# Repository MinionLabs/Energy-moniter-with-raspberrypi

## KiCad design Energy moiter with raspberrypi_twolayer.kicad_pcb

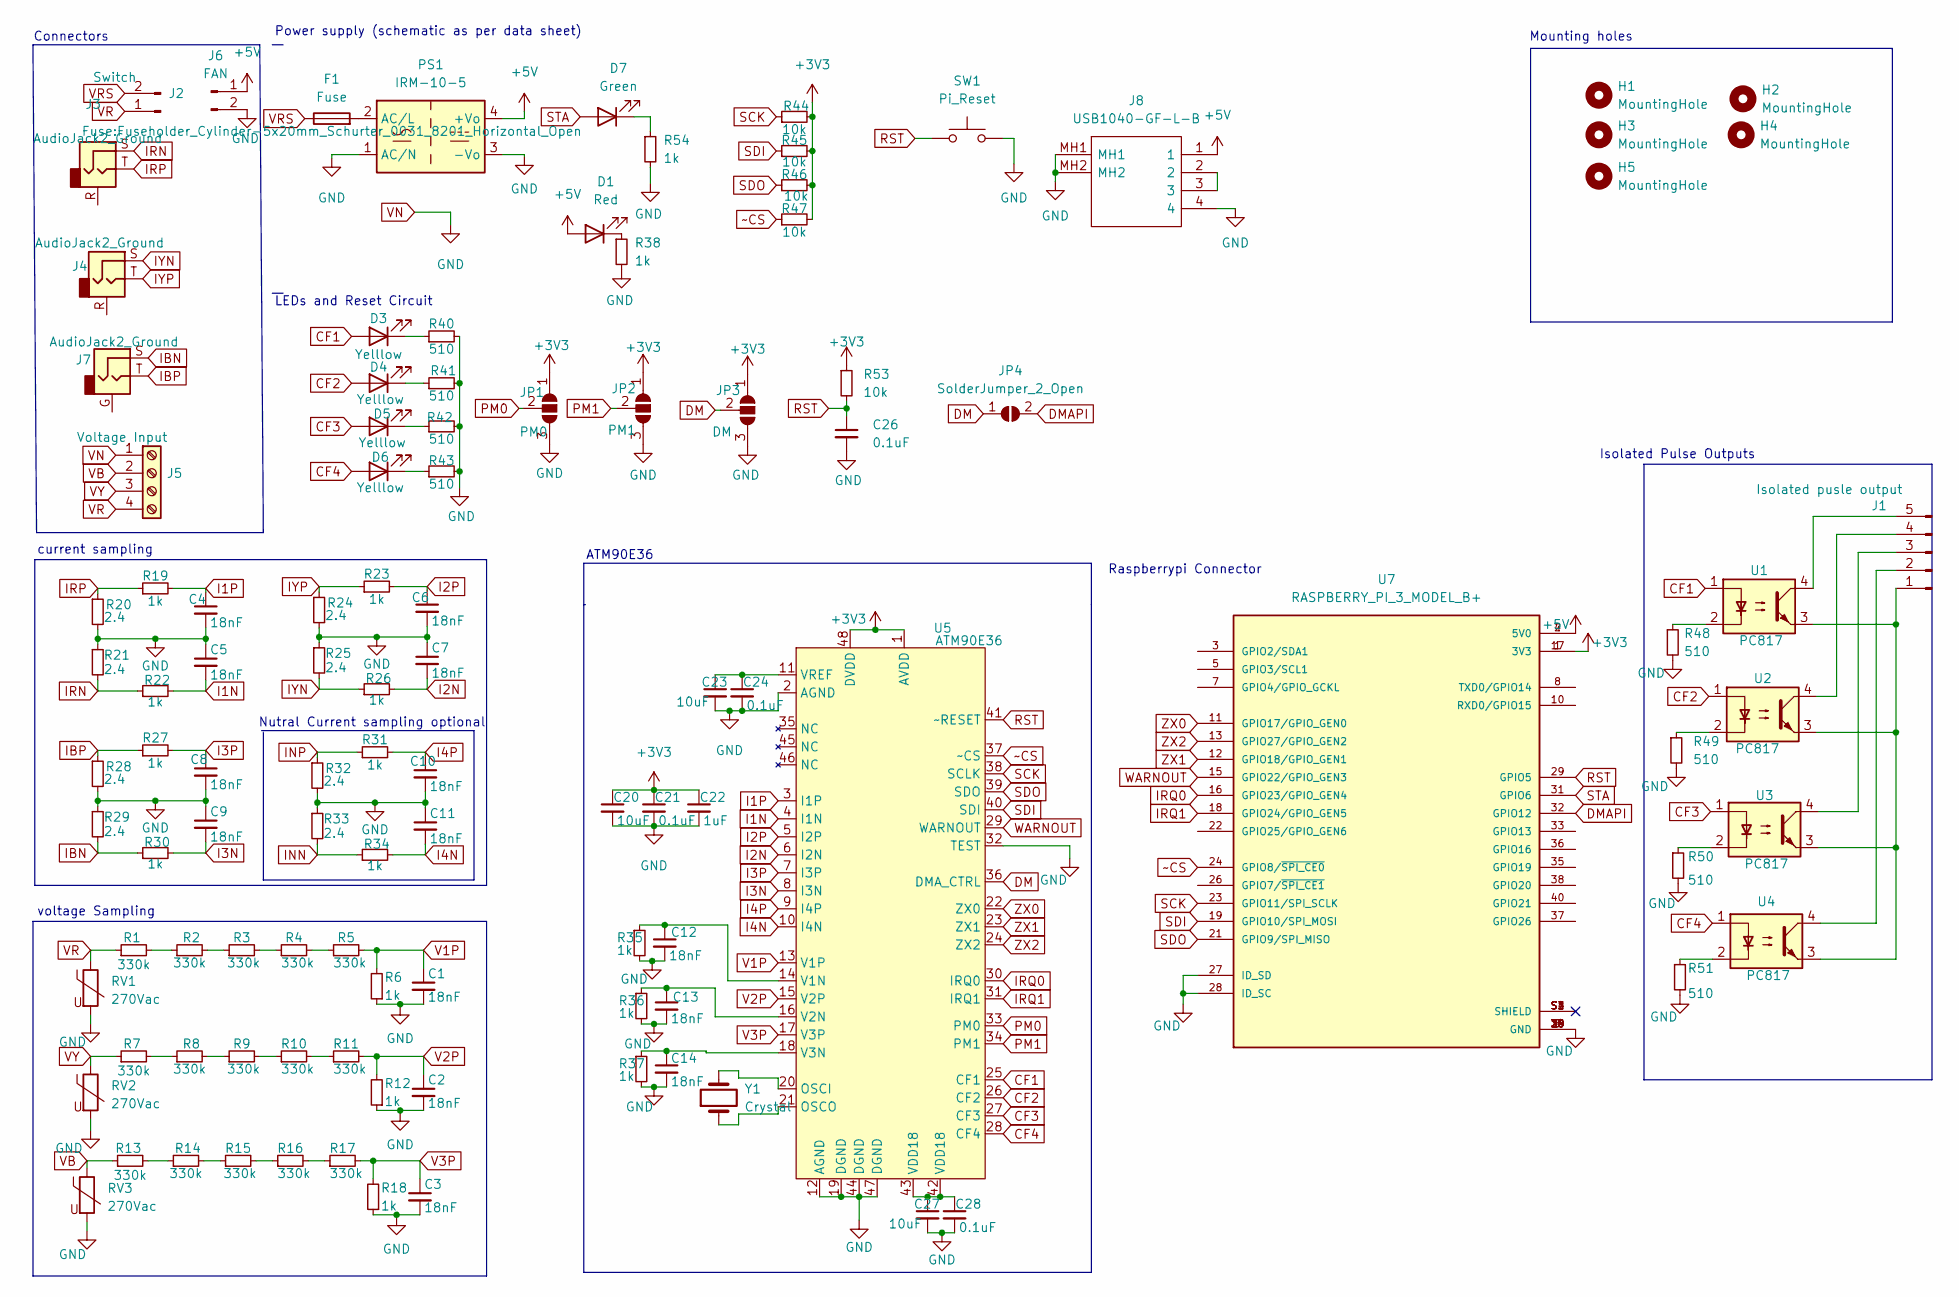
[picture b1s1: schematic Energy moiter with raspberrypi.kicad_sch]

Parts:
C1, C2, C3, C4, C5, C6, C7, C8, C9, C10, C11, C12, C13, C14: 18nF; C_0603_1608Metric
C20, C23, C27: 10uF; C_0603_1608Metric
C21, C24, C26, C28: 0.1uF; C_0603_1608Metric
C22: 1uF; C_0603_1608Metric
D1: Red; LED_0603_1608Metric_Pad1.05x0.95mm_HandSolder
D3, D4, D5, D6: Yelllow; LED_0603_1608Metric_Pad1.05x0.95mm_HandSolder
D7: Green; LED_0603_1608Metric_Pad1.05x0.95mm_HandSolder
F1: Fuse; Fuseholder_Cylinder-5x20mm_Schurter_0031_8201_Horizontal_Op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
H1, H2, H3, H4, H5: MountingHole; MountingHole_3.5mm
J1: Isolated pusle output; PinHeader_1x05_P2.54mm_Vertical
J2: Switch; JST_EH_B2B-EH-A_1x02_P2.50mm_Vertical
J3, J4, J7: AudioJack2_Ground; Jack_3.5mm_PJ320D_Horizontal
J5: Voltage Input; PhoenixContact_MSTBA_2,5_4-G-5,08_1x04_P5.08mm_Horizontal
J6: FAN; JST_EH_B2B-EH-A_1x02_P2.50mm_Vertical
J8: USB1040-GF-L-B; USB1040GFLB; Manufacturer_Part_Number USB1040-GF-L-B; Mouser Part Number 640-USB1040-GF-L-B
JP1: PM0; SolderJumper-3_P1.3mm_Open_RoundedPad1.0x1.5mm_NumberLabels
JP2: PM1; SolderJumper-3_P1.3mm_Open_RoundedPad1.0x1.5mm_NumberLabels
JP3: DM; SolderJumper-3_P1.3mm_Open_RoundedPad1.0x1.5mm_NumberLabels
JP4: SolderJumper_2_Open; SolderJumper-2_P1.3mm_Open_RoundedPad1.0x1.5mm
PS1: IRM-10-5; Converter_ACDC_MeanWell_IRM-10-xx_THT
R1, R2, R3, R4, R5, R7, R8, R9, R10, R11, R13, R14, R15, R16, R17: 330k; R_1206_3216Metric
R6, R12, R18: 1k; R_1206_3216Metric
R19, R22, R23, R26, R27, R30, R31, R34, R35, R36, R37, R38, R54: 1k; R_0603_1608Metric
R20, R21, R24, R25, R28, R29, R32, R33: 2.4; R_1206_3216Metric
R40, R41, R42, R43, R48, R49, R50, R51: 510; R_0603_1608Metric
R44, R45, R46, R47, R53: 10k; R_0603_1608Metric
RV1, RV2, RV3: 270Vac; RV_Disc_D15.5mm_W4.6mm_P7.5mm
SW1: Pi_Reset; SW_Push_1P1T_NO_6x6mm_H9.5mm
U1, U2, U3, U4: PC817; SSO-4_6.7x5.1mm_P2.54mm_Clearance8mm
U5: ATM90E36; LQFP-48_7x7mm_P0.5mm
U7: RASPBERRY_PI_3_MODEL_B+; MODULE_RASPBERRY_PI_3_MODEL_B+; PARTREV 1.0
Y1: Crystal; Crystal_SMD_Abracon_ABM3-2Pin_5.0x3.2mm

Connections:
+3V3: C20.1, C21.1, C22.1, JP1.1 (A), JP2.1 (A), JP3.1 (A), R44.2, R45.2, R46.2, R47.2, R53.1, U5.1 (AVDD), U5.48 (DVDD), U7.1 (3V3), U7.17 (3V3)
+5V: D1.2 (A), J6.1, J8.1, PS1.4 (+Vo), U7.2 (5V0), U7.4 (5V0)
CF1: D3.2 (A), U1.1, U5.25 (CF1)
CF2: D4.2 (A), U2.1, U5.26 (CF2)
CF3: D5.2 (A), U3.1, U5.27 (CF3)
CF4: D6.2 (A), U4.1, U5.28 (CF4)
DM: JP3.2 (C), JP4.1 (A), U5.36 (DMA_CTRL)
DMAPI: JP4.2 (B), U7.32 (GPIO12)
I1N: C5.2, R22.2, U5.4 (I1N)
I1P: C4.1, R19.2, U5.3 (I1P)
I2N: C7.2, R26.2, U5.6 (I2N)
I2P: C6.1, R23.2, U5.5 (I2P)
I3N: C9.2, R30.2, U5.8 (I3N)
I3P: C8.1, R27.2, U5.7 (I3P)
I4N: C11.2, R34.2, U5.10 (I4N)
I4P: C10.1, R31.2, U5.9 (I4P)
IBN: J7.S, R29.2, R30.1
IBP: J7.T, R27.1, R28.1
INN: R33.2, R34.1
INP: R31.1, R32.1
IRN: J3.S, R21.2, R22.1
IRP: J3.T, R19.1, R20.1
IRQ0: U5.30 (IRQ0), U7.16 (GPIO23/GPIO_GEN4)
IRQ1: U5.31 (IRQ1), U7.18 (GPIO24/GPIO_GEN5)
IYN: J4.S, R25.2, R26.1
IYP: J4.T, R23.1, R24.1
unnamed: C12.1, R35.1, U5.14 (V1N)
unnamed: C13.1, R36.1, U5.16 (V2N)
unnamed: C14.1, R37.1, U5.18 (V3N)
unnamed: C23.1, C24.1, U5.11 (VREF)
unnamed: C27.1, C28.1, U5.42 (VDD18), U5.43 (VDD18)
unnamed: D1.1 (K), R38.1
unnamed: D3.1 (K), R40.1
unnamed: D4.1 (K), R41.1
unnamed: D5.1 (K), R42.1
unnamed: D6.1 (K), R43.1
unnamed: D7.1 (K), R54.1
unnamed: F1.2, PS1.2 (AC/L)
unnamed: J1.1, U1.3, U2.3, U3.3, U4.3
unnamed: J1.2, U4.4
unnamed: J1.3, U3.4
unnamed: J1.4, U2.4
unnamed: J1.5, U1.4
unnamed: J8.2, J8.3
unnamed: R1.2, R2.1
unnamed: R2.2, R3.1
unnamed: R3.2, R4.1
unnamed: R4.2, R5.1
unnamed: R7.2, R8.1
unnamed: R8.2, R9.1
unnamed: R9.2, R10.1
unnamed: R10.2, R11.1
unnamed: R13.2, R14.1
unnamed: R14.2, R15.1
unnamed: R15.2, R16.1
unnamed: R16.2, R17.1
unnamed: R48.1, U1.2
unnamed: R49.1, U2.2
unnamed: R50.1, U3.2
unnamed: R51.1, U4.2
unnamed: U5.20 (OSCI), Y1.2
unnamed: U5.21 (OSCO), Y1.1
PM0: JP1.2 (C), U5.33 (PM0)
PM1: JP2.2 (C), U5.34 (PM1)
RST: C26.1, R53.2, SW1.1, U5.41 (~RESET), U7.29 (GPIO5)
SCK: R44.1, U5.38 (SCLK), U7.23 (GPIO11/SPI_SCLK)
SDI: R45.1, U5.40 (SDI), U7.19 (GPIO10/SPI_MOSI)
SDO: R46.1, U5.39 (SDO), U7.21 (GPIO9/SPI_MISO)
STA: D7.2 (A), U7.31 (GPIO6)
V1P: C1.1, R5.2, R6.2, U5.13 (V1P)
V2P: C2.1, R11.2, R12.2, U5.15 (V2P)
V3P: C3.1, R17.2, R18.2, U5.17 (V3P)
VB: J5.2, R13.1, RV3.1
VN: C1.2, C2.2, C3.2, C4.2, C5.1, C6.2, C7.1, C8.2, C9.1, C10.2, C11.1, C12.2, C13.2, C14.2, C20.2, C21.2, C22.2, C23.2, C24.2, C26.2, C27.2, C28.2, J5.1, J6.2, J8.4, J8.MH1, J8.MH2, JP1.3 (B), JP2.3 (B), JP3.3 (B), PS1.1 (AC/N), PS1.3 (-Vo), R6.1, R12.1, R18.1, R20.2, R21.1, R24.2, R25.1, R28.2, R29.1, R32.2, R33.1, R35.2, R36.2, R37.2, R38.2, R40.2, R41.2, R42.2, R43.2, R48.2, R49.2, R50.2, R51.2, R54.2, RV1.2, RV2.2, RV3.2, SW1.2, U5.2 (AGND), U5.12 (AGND), U5.19 (DGND), U5.32 (TEST), U5.44 (DGND), U5.47 (DGND), U7.6 (GND), U7.9 (GND), U7.14 (GND), U7.20 (GND), U7.25 (GND), U7.27 (ID_SD), U7.28 (ID_SC), U7.30 (GND), U7.34 (GND), U7.39 (GND)
VR: J2.1, J5.4, R1.1, RV1.1
VRS: F1.1, J2.2
VY: J5.3, R7.1, RV2.1
WARNOUT: U5.29 (WARNOUT), U7.15 (GPIO22/GPIO_GEN3)
ZX0: U5.22 (ZX0), U7.11 (GPIO17/GPIO_GEN0)
ZX1: U5.23 (ZX1), U7.12 (GPIO18/GPIO_GEN1)
ZX2: U5.24 (ZX2), U7.13 (GPIO27/GPIO_GEN2)
~CS: R47.1, U5.37 (~CS), U7.24 (GPIO8/~SPI_CE0)

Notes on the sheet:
ATM90E36
Power supply (schematic as per data sheet)
current sampling
Connectors
voltage Sampling
Raspberrypi Connector
Isolated Pulse Outputs
LEDs and Reset Circuit
Nutral Current sampling optional
Mounting holes

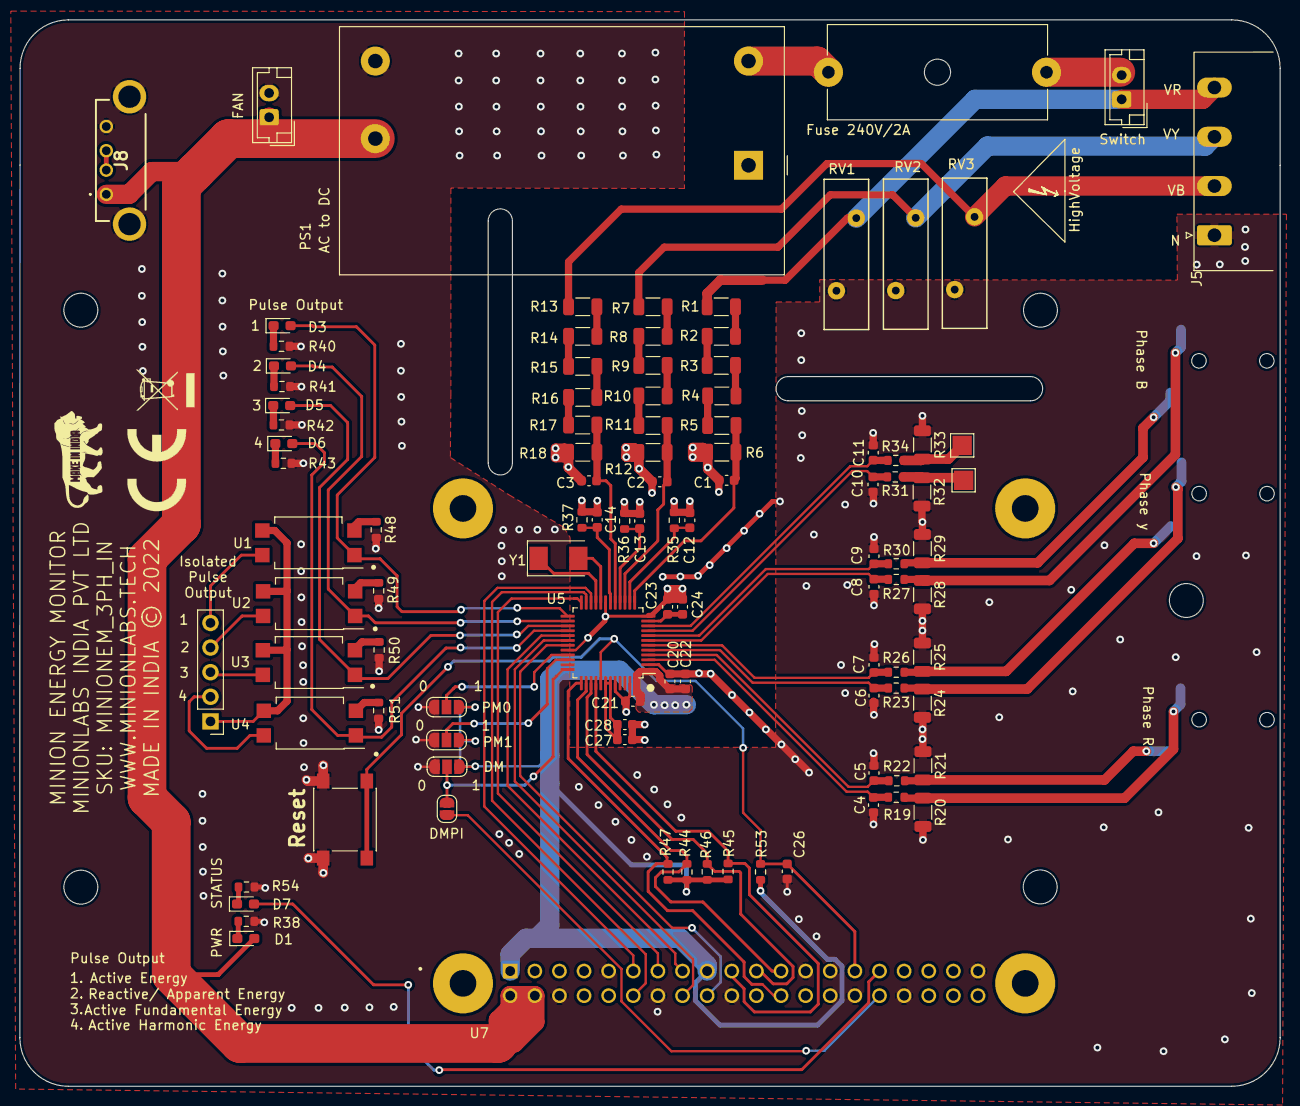
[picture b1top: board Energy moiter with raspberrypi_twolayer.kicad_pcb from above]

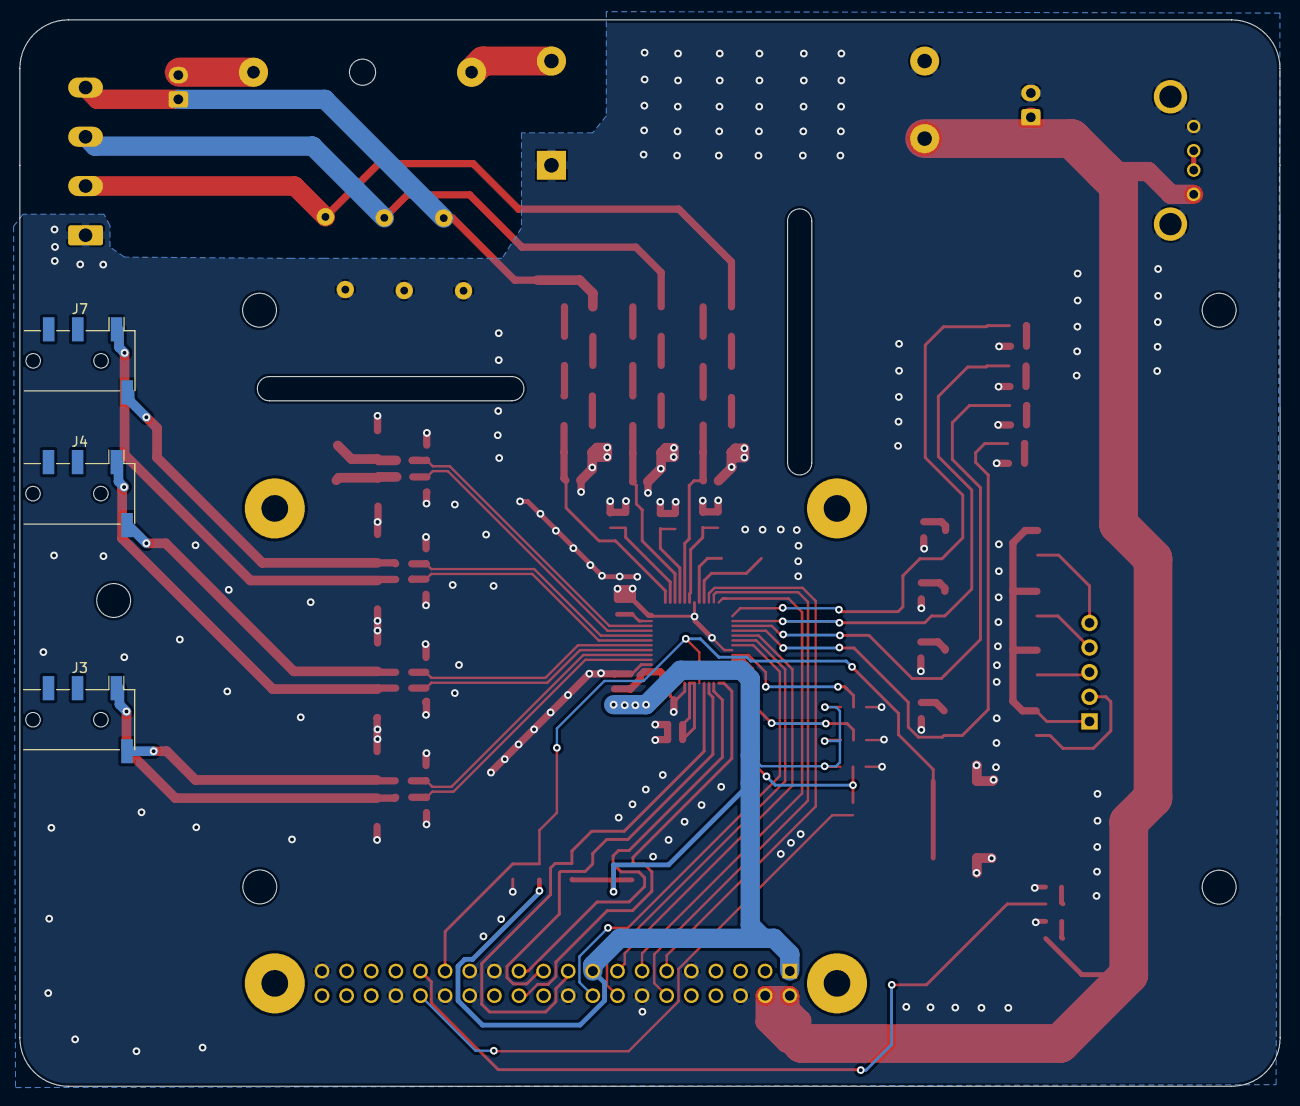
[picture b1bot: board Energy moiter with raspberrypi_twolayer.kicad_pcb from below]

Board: 2 copper layers, 130.0 x 110.0 mm, 110 parts (3 on the bottom side), 82 nets.

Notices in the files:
Energy moiter with raspberrypi_twolayer.kicad_pcb:
MADE IN INDIA © 2022
